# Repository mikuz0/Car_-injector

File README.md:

# Car_-injector
Програмное обеспечение самодельного стенда для промывки форсунок.</br>
В качестве железа использовалься RGBW контроллер, проект KiCAD прилагается.</br>
Можно исползовать <a href="http://www.mkuznecov.ru/file/rgbw-shild-dlya-arduino-nano.html" >  RGB(W) шильд для Arduino-nano </a> </br>
Нербходимо добавить защитные диоды. </br>

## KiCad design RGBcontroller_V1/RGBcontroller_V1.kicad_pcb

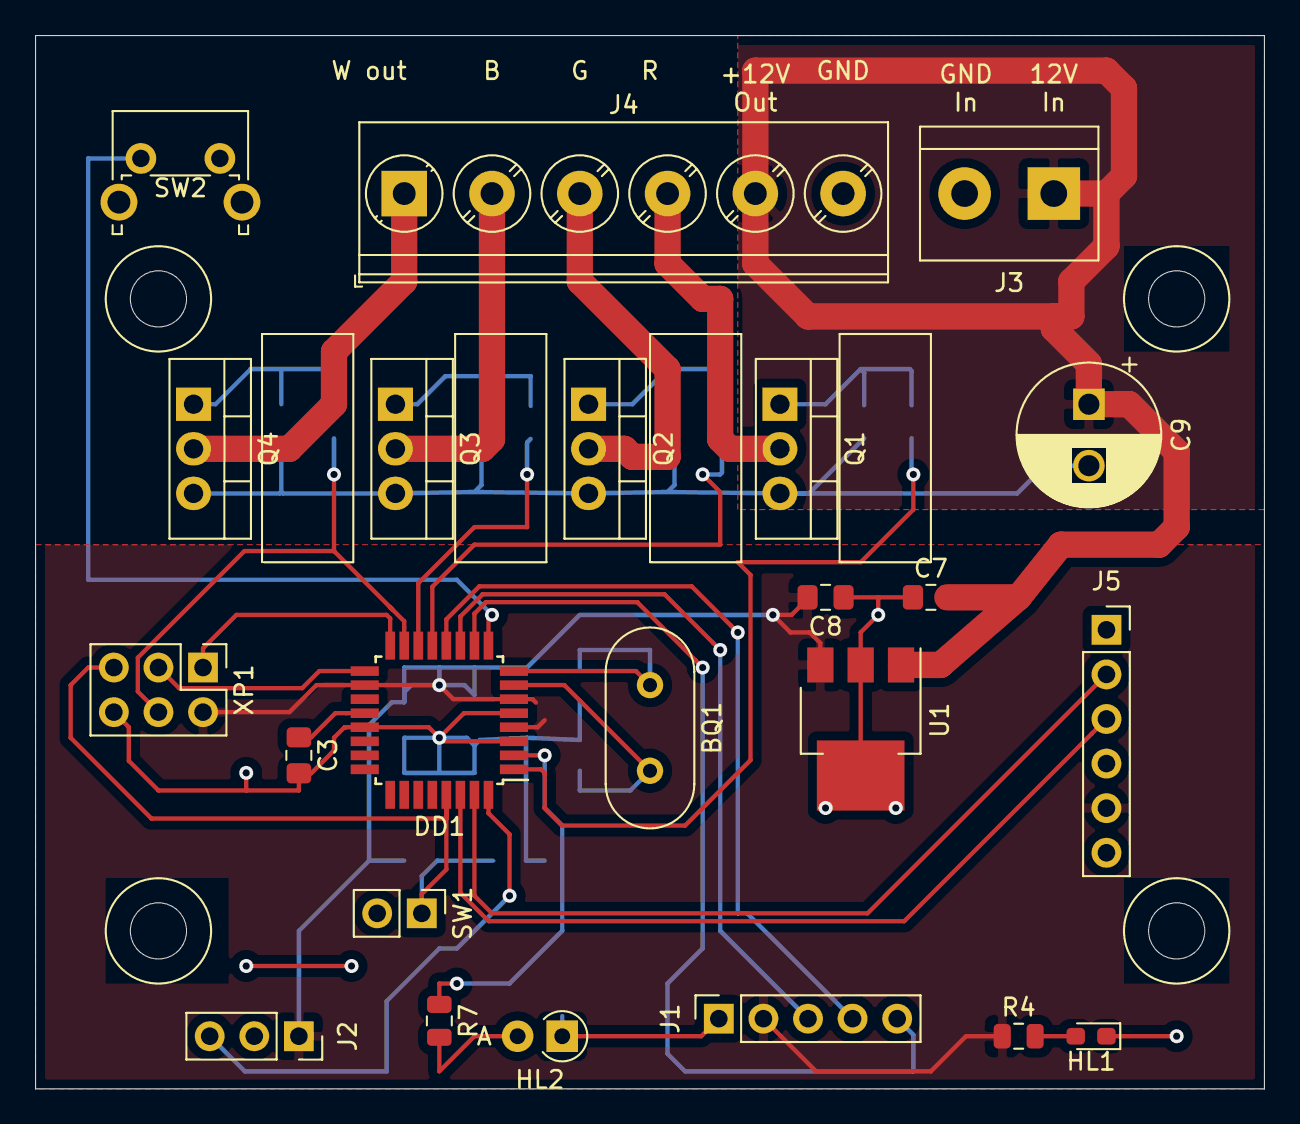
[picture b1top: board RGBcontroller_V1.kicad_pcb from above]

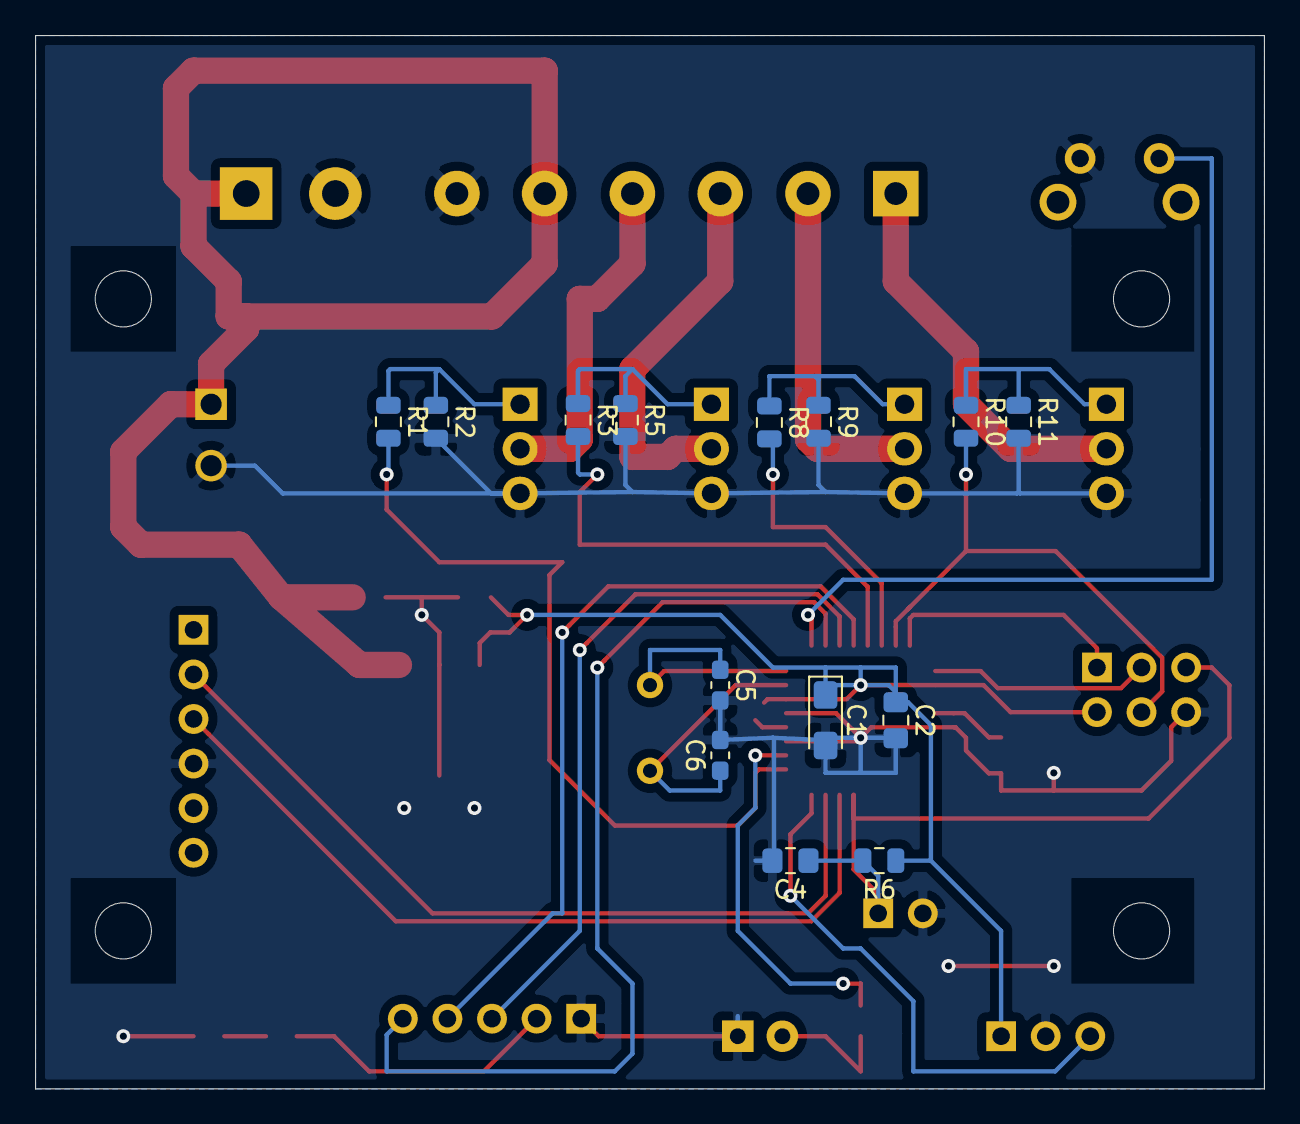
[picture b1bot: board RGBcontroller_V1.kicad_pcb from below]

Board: 2 copper layers, 70.0 x 60.0 mm, 37 parts (14 on the bottom side), 31 nets.

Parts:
BQ1: Crystal; Crystal_HC49-4H_Vertical
C1: 10мкФ; CP_EIA-3216-18_Kemet-A_Pad1.58x1.35mm_HandSolder
C2, C3, C4, C7, C8: 0,1 мкФ; C_0805_2012Metric_Pad1.15x1.40mm_HandSolder
C5, C6: 22пФ; C_0603_1608Metric_Pad1.05x0.95mm_HandSolder
C9: 1000мкФ; CP_Radial_D8.0mm_P3.50mm
DD1: ATMEGA328P-A; TQFP-32_7x7mm_P0.8mm
HL1: LED; LED_0603_1608Metric_Pad1.05x0.95mm_HandSolder
HL2: LED; D_A-405_P2.54mm_Vertical_AnodeUp
J1: ЭНКОДЕР; PinSocket_1x05_P2.54mm_Vertical
J2: Conn_01x03; PinSocket_1x03_P2.54mm_Vertical
J3: Conn_01x02; TerminalBlock_bornier-2_P5.08mm
J4: Screw_Terminal_01x06; TerminalBlock_Phoenix_PT-1,5-6-5.0-H_1x06_P5.00mm_Horizontal
J5: Conn_01x06_Female; PinSocket_1x06_P2.54mm_Vertical
Q1, Q2, Q3, Q4: IRF540N; TO-220-3_Vertical
R1, R3, R6, R8, R10: 10 кОм; R_0805_2012Metric
R2, R5, R9, R11: 100 кОм; R_0805_2012Metric
R4: 680 Ом; R_0805_2012Metric
R7: 270 Ом; R_0805_2012Metric
SW1: SW_DIP_x01-Switch-RDC1-0035-rescue; PinHeader_1x02_P2.54mm_Vertical
SW2: SW_DIP_x01; SW_Tactile_SPST_Angled_PTS645Vx83-2LFS
U1: L78M05ABDT; SOT-223-3_TabPin2
XP1: CONN_02X03; PinHeader_2x03_P2.54mm_Vertical

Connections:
12V_P: C7.2, C9.1, J3.1, J4.5, U1.1
B: J4.2, Q3.2
BT_Rx: DD1.31, J5.2
BT_Tx: DD1.30, J5.3
D3: DD1.1, R1.2
D4: DD1.2, R7.1
D5: DD1.9, SW2.1
D6: DD1.10, J1.5
D7: DD1.11, J1.3
D8: DD1.12, J1.4
D9: DD1.13, R3.2
D10: DD1.14, R8.2
D11: DD1.15, R10.2, XP1.4
D12/MISO: DD1.16, XP1.1
D13/SCK: DD1.17, XP1.3
G: J4.3, Q2.2
GND: C1.2, C2.2, C3.2, C4.2, C5.2, C6.2, C7.1, C8.1, C9.2, DD1.3, DD1.5, DD1.21, HL1.1, HL2.1, J1.1, J2.2, J3.2, J4.6, J5.4, Q1.3, Q2.3, Q3.3, Q4.3, R2.2, R5.2, R9.2, R11.2, SW1.2, SW2.2, U1.2, XP1.6
IRED: DD1.32, J2.3
unnamed: BQ1.1, C5.1, DD1.8
unnamed: BQ1.2, C6.1, DD1.7
unnamed: C3.1, DD1.20
unnamed: HL1.2, R4.2
unnamed: HL2.2, R7.2
unnamed: Q1.1, R1.1, R2.1
unnamed: Q2.1, R3.1, R5.1
unnamed: Q3.1, R8.1, R9.1
unnamed: Q4.1, R10.1, R11.1
R: J4.4, Q1.2
RES: C4.1, DD1.29, R6.2, SW1.1, XP1.5
VDD: C1.1, C2.1, C8.2, DD1.4, DD1.6, DD1.18, J1.2, J2.1, J5.5, R4.1, R6.1, U1.3, XP1.2
W: J4.1, Q4.2
